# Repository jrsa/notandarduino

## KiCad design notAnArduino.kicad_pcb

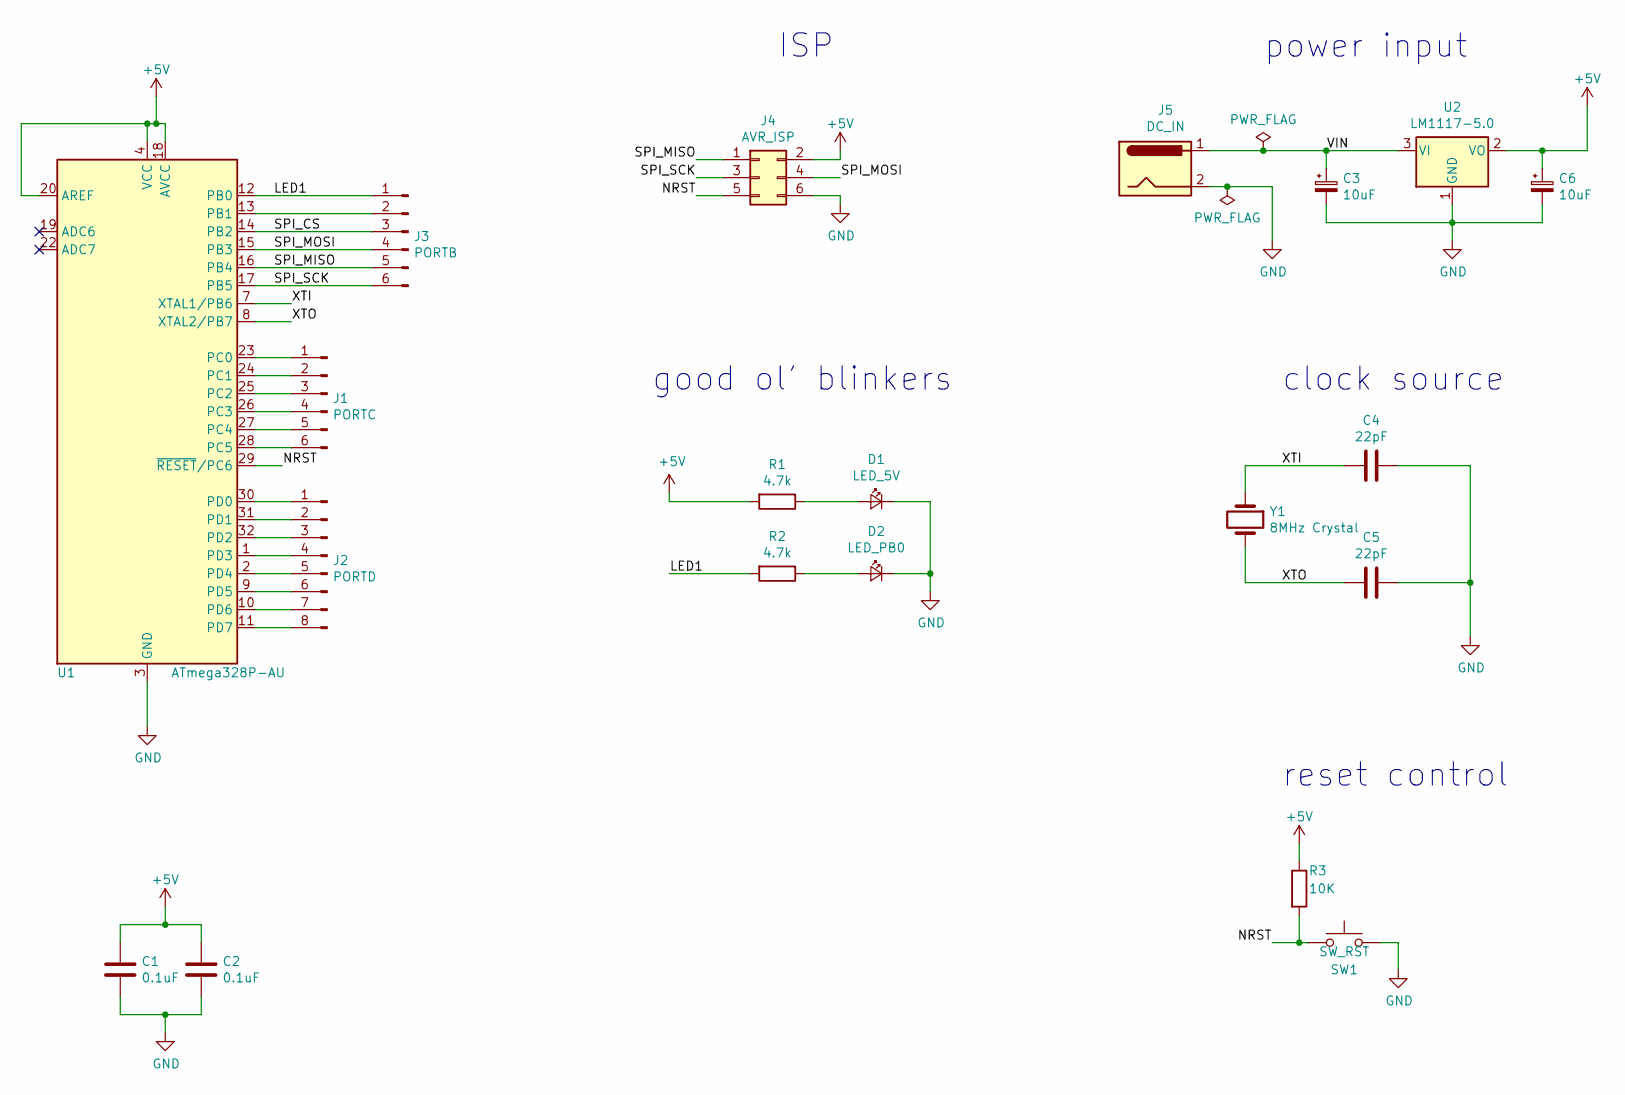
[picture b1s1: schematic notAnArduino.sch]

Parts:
C1, C2: 0.1uF; C_0603_1608Metric
C3, C6: 10uF; CP_Elec_5x3.9
C4, C5: 22pF; C_0603_1608Metric
D1: LED_5V; LED_1206_3216Metric
D2: LED_PB0; LED_1206_3216Metric
J1: PORTC; PinHeader_1x06_P2.54mm_Vertical_SMD_Pin1Right
J2: PORTD; PinHeader_1x08_P2.54mm_Vertical_SMD_Pin1Left
J3: PORTB; PinHeader_1x06_P2.54mm_Vertical_SMD_Pin1Left
J4: AVR_ISP; PinHeader_2x03_P2.54mm_Vertical_SMD
J5: DC_IN; BarrelJack_CUI_PJ-036AH-SMT_Horizontal
R1, R2: 4.7k; R_0603_1608Metric
R3: 10K; R_0603_1608Metric
SW1: SW_RST; SW_Push_1P1T-SH_NO_CK_KMR2xxG
U1: ATmega328P-AU; TQFP-32_7x7mm_P0.8mm
U2: LM1117-5.0; SOT-223
Y1: 8MHz Crystal; Crystal_SMD_0603-4Pin_6.0x3.5mm

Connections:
+5V: C1.1, C2.1, C6.1, J4.2, R1.2, R3.1, U1.4 (VCC), U1.6 (VCC), U1.18 (AVCC), U1.20 (AREF), U2.2 (VO)
/LED1: J3.1, R2.2, U1.12 (PB0)
/NRST: J4.5, R3.2, SW1.1, U1.29 (~RESET~/PC6)
/SPI_CS: J3.3, U1.14 (PB2)
/SPI_MISO: J3.5, J4.1, U1.16 (PB4)
/SPI_MOSI: J3.4, J4.4, U1.15 (PB3)
/SPI_SCK: J3.6, J4.3, U1.17 (PB5)
/VIN: C3.1, J5.1, U2.3 (VI)
/XTI: C4.2, U1.7 (XTAL1/PB6), Y1.1
/XTO: C5.2, U1.8 (XTAL2/PB7), Y1.2
GND: C1.2, C2.2, C3.2, C4.1, C5.1, C6.2, D1.1 (K), D2.1 (K), J4.6, J5.2, SW1.2, U1.3 (GND), U1.5 (GND), U1.21 (GND), U2.1 (GND)
unnamed: D1.2 (A), R1.1
unnamed: D2.2 (A), R2.1
unnamed: J1.1, U1.23 (PC0)
unnamed: J1.2, U1.24 (PC1)
unnamed: J1.3, U1.25 (PC2)
unnamed: J1.4, U1.26 (PC3)
unnamed: J1.5, U1.27 (PC4)
unnamed: J1.6, U1.28 (PC5)
unnamed: J2.1, U1.30 (PD0)
unnamed: J2.2, U1.31 (PD1)
unnamed: J2.3, U1.32 (PD2)
unnamed: J2.4, U1.1 (PD3)
unnamed: J2.5, U1.2 (PD4)
unnamed: J2.6, U1.9 (PD5)
unnamed: J2.7, U1.10 (PD6)
unnamed: J2.8, U1.11 (PD7)
unnamed: J3.2, U1.13 (PB1)

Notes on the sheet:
power input
clock source
reset control
ISP
good ol' blinkers

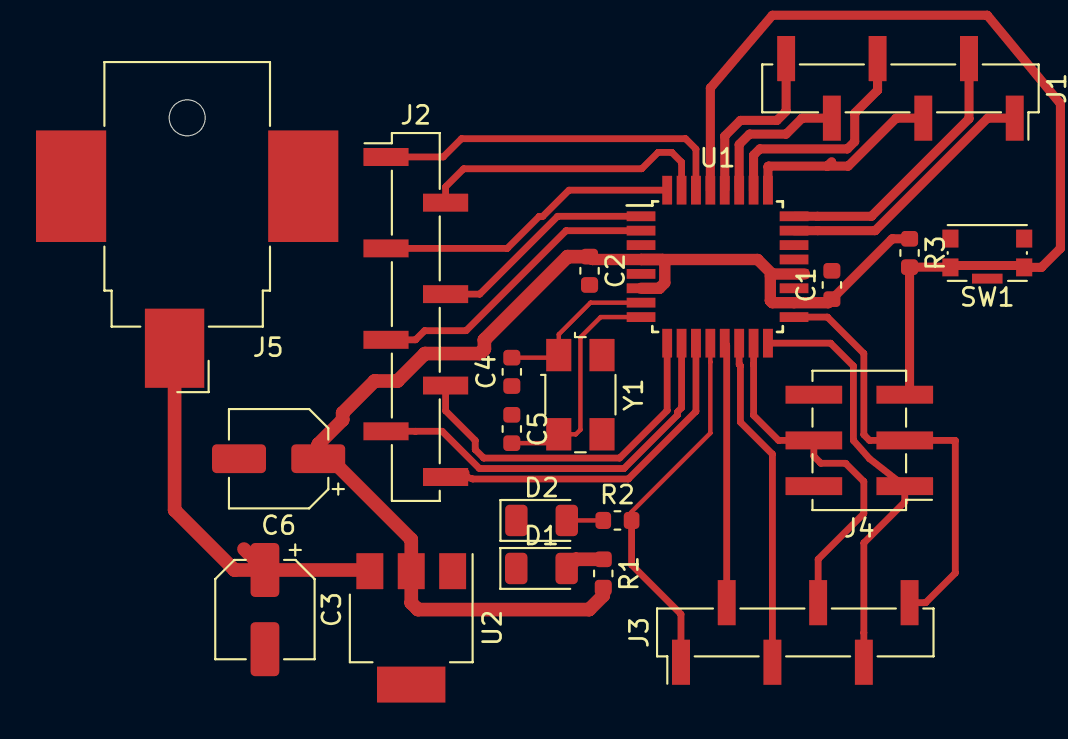
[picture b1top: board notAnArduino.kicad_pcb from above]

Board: 2 copper layers, 20 parts (0 on the bottom side), 28 nets.

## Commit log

2020-03-10 initial, layout is bokren
2020-03-11 re layed out?? hehe
